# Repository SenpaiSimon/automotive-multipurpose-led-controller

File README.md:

# Multipurpose Controller for Cars multimedia

Functions present on the board: 

- 5 LED Controller Ports for WS2811
- Controllable Subwoofer Audio Singal Damper
- Switch to toggle Subwoofer Amplifier on and off
- Bluetooth Module to Control
- Atmega Microcontroller with UART Bridge
- Direct Voltage input from car battery

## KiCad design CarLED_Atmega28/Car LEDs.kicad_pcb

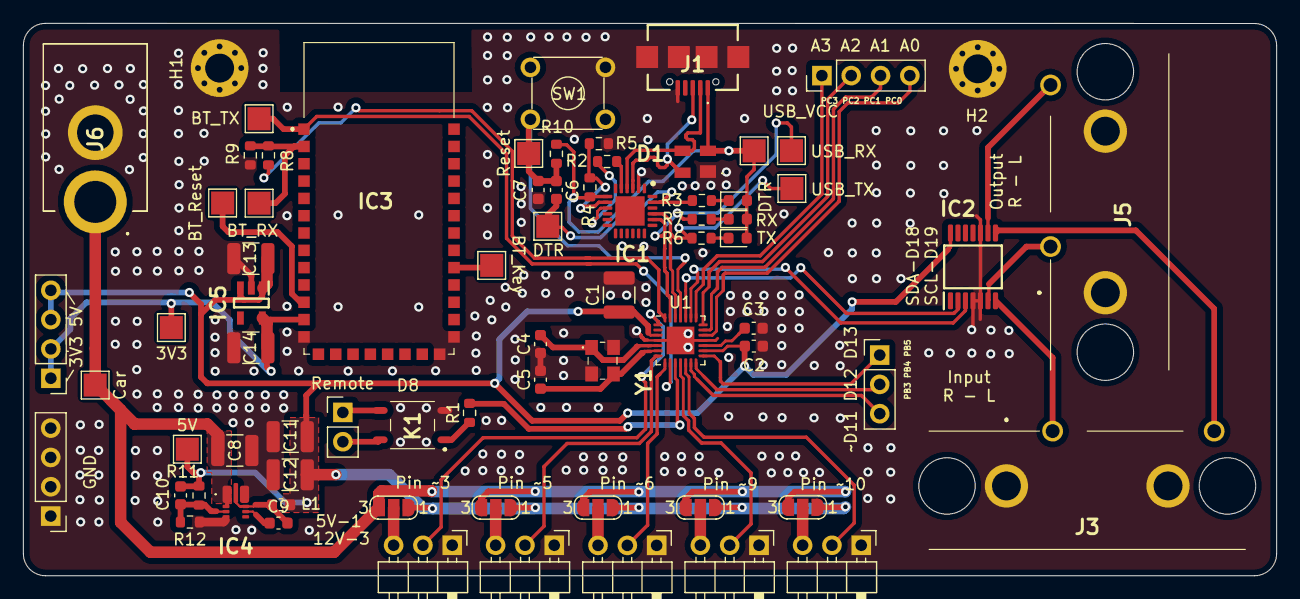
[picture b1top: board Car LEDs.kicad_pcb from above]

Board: 2 copper layers, 108.6 x 47.9 mm, 73 parts (0 on the bottom side), 55 nets.

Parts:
C1, C8: 10u; C_1210_3225Metric
C2, C3, C6, C7, C9: 100n; C_0603_1608Metric
C4, C5: 8p; C_0603_1608Metric
C10: 47p; C_0603_1608Metric
C11, C12: 22u; C_1210_3225Metric
C13, C14: 1u; C_1210_3225Metric
D1: SP0503BAHTG
DTR: RED; LED_0603_1608Metric
H1, H2: MountingHole_Pad; MountingHole_2.5mm_Pad_Via
IC1: CP2102N-A02-GQFN24R; QFN50P400X400X80-25N-D
IC2: MCP4631-502E_ST; SOP65P640X120-14N
IC3: BLUETOOTH-SERIAL-HC-06; BLUETOOTHSERIALHC06
IC4: AP63356DV-7; AP63356DV7
IC5: AP7343DQ-33W5-7; SOT95P285X140-5N
J1: USB_B_Micro; UJ2MIBHGSMTTR
J2: Remote; PinHeader_1x02_P2.54mm_Vertical
J3: Input; RCJ2121
J4: IO; PinHeader_1x04_P2.54mm_Vertical
J5: Output; RCJ2121
J6: CAR_Jack; PJ037A
J7: LED1_Pin3; PinHeader_1x03_P2.54mm_Horizontal
J8: LED2_Pin5; PinHeader_1x03_P2.54mm_Horizontal
J9: LED3_Pin6; PinHeader_1x03_P2.54mm_Horizontal
J10: LED4_Pin9; PinHeader_1x03_P2.54mm_Horizontal
J11: LED5_Pin10; PinHeader_1x03_P2.54mm_Horizontal
J12: IO2; PinHeader_1x03_P2.54mm_Vertical
J13: Power; PinHeader_1x04_P2.54mm_Vertical
J14: GND; PinHeader_1x04_P2.54mm_Vertical
JP1, JP2, JP3, JP4, JP5: VCC; SolderJumper-3_P1.3mm_Open_RoundedPad1.0x1.5mm_NumberLabels
K1: CPC1125NTR
L1: 6.8u; L_0603_1608Metric
R1: 750; R_0603_1608Metric
R2, R8: 1k; R_0603_1608Metric
R3, R6, R7: 220; R_0603_1608Metric
R4: 22.1k; R_0603_1608Metric
R5: 47.5k; R_0603_1608Metric
R9: 2k; R_0603_1608Metric
R10: 10k; R_0603_1608Metric
R11: 157k; R_0603_1608Metric
R12: 30k; R_0603_1608Metric
RX: GREEN; LED_0603_1608Metric
SW1: SW_Push; Button_Omron
TP2: RX; TestPoint_Pad_2.0x2.0mm
TP3: TX; TestPoint_Pad_2.0x2.0mm
TP4: USBVCC; TestPoint_Pad_2.0x2.0mm
TP5: DTR; TestPoint_Pad_2.0x2.0mm
TP6: Jack; TestPoint_Pad_2.0x2.0mm
TP7: Reset; TestPoint_Pad_2.0x2.0mm
TP8: BT_Key; TestPoint_Pad_2.0x2.0mm
TP9: BT_Reset; TestPoint_Pad_2.0x2.0mm
TP10: 5V; TestPoint_Pad_2.0x2.0mm
TP11: 3V3; TestPoint_Pad_2.0x2.0mm
TP12: BT_TX; TestPoint_Pad_2.0x2.0mm
TP13: BT_RX; TestPoint_Pad_2.0x2.0mm
TX: GREEN; LED_0603_1608Metric
U1: ATmega328-MMH; QFN-28-1EP_4x4mm_P0.45mm_EP2.4x2.4mm
Y1: ECS-160-9-33B-CKM-TR; ECS2501033BCKMTR

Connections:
3V3: C14.1, IC3.12, IC5.5, J13.1, J13.2, TP11.1
5V: C1.1, C2.1, C10.1, C11.1, C12.1, C13.1, IC2.14, IC5.1, IC5.3, J13.3, J13.4, JP1.1, JP2.1, JP3.1, JP4.1, JP5.1, L1.2, R11.1, TP10.1, U1.3, U1.16
BT_RX: IC3.2, R8.2, R9.1, TP13.1
BT_TX: IC3.1, TP12.1, U1.9
CAR_Power: C8.1, IC4.1, IC4.2, J6.1, JP1.3, JP2.3, JP3.3, JP4.3, JP5.3, TP6.1
D+: D1.4, IC1.3, J1.3
D-: D1.3, IC1.4, J1.2
DTR: C6.2, IC1.23, R3.2, TP5.1
Data1: J7.2, U1.1
Data2: J8.2, U1.7
Data3: J9.2, U1.8
Data4: J10.2, U1.11
Data5: J11.2, U1.12
GND: C1.2, C2.2, C3.2, C4.1, C5.2, C7.2, C8.2, C11.2, C12.2, C13.2, C14.2, D1.1, H1.1, H2.1, IC1.2, IC2.4, IC2.5, IC2.10, IC3.13, IC3.21, IC3.22, IC4.4, IC4.8, IC5.2, J1.5, J1.6, J3.1, J3.3, J5.1, J5.3, J6.2, J7.1, J8.1, J9.1, J10.1, J11.1, J14.1, J14.2, J14.3, J14.4, K1.2, R5.2, R9.2, R12.2, SW1.2, U1.4, U1.18, U1.29, Y1.2, Y1.4
L_IN: IC2.8, J3.4
L_OUT: IC2.9, J5.4
unnamed: C3.1, U1.17
unnamed: C4.2, U1.5, Y1.1
unnamed: C5.1, U1.6, Y1.3
unnamed: C9.1, IC4.6
unnamed: C9.2, IC4.9, L1.1
unnamed: C10.2, IC4.3, R11.2, R12.1
unnamed: DTR.1, R3.1
unnamed: R6.2, TX.1
unnamed: R7.2, RX.1
unnamed: IC1.5, R2.1
unnamed: IC1.8, R4.2, R5.1
unnamed: IC1.9, R2.2
unnamed: IC3.11, TP9.1
unnamed: IC3.26, TP8.1
unnamed: J2.1, K1.3
unnamed: J2.2, K1.4
unnamed: J4.1, U1.22
unnamed: J4.2, U1.21
unnamed: J4.3, U1.20
unnamed: J4.4, U1.19
unnamed: J7.3, JP1.2
unnamed: J8.3, JP2.2
unnamed: J9.3, JP3.2
unnamed: J10.3, JP4.2
unnamed: J11.3, JP5.2
unnamed: J12.1, U1.15
unnamed: J12.2, U1.14
unnamed: J12.3, U1.13
unnamed: K1.1, R1.1
unnamed: R8.1, U1.28
R_IN: IC2.7, J3.2
R_OUT: IC2.6, J5.2
RemoteON: R1.2, U1.10
Reset: C6.1, C7.1, R10.2, SW1.1, TP7.1, U1.25
SCL: IC2.2, U1.24
SDA: IC2.3, U1.23
USB_RX: IC1.20, R7.1, TP2.1, U1.27
USB_TX: IC1.21, R6.1, TP3.1, U1.26
USB_VCC: D1.2, DTR.2, IC1.7, J1.1, R4.1, R10.1, RX.2, TP4.1, TX.2

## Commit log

2022-04-07 inititial commit
2022-05-12 bumped kicad version
2022-05-16 version bumb
